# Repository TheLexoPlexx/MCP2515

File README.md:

# MCP2515
KiCad-Files for the commonly found MCP2515 CAN Controller and Transceiver used in plenty of arduino-Projects.

Schematic is not my own.

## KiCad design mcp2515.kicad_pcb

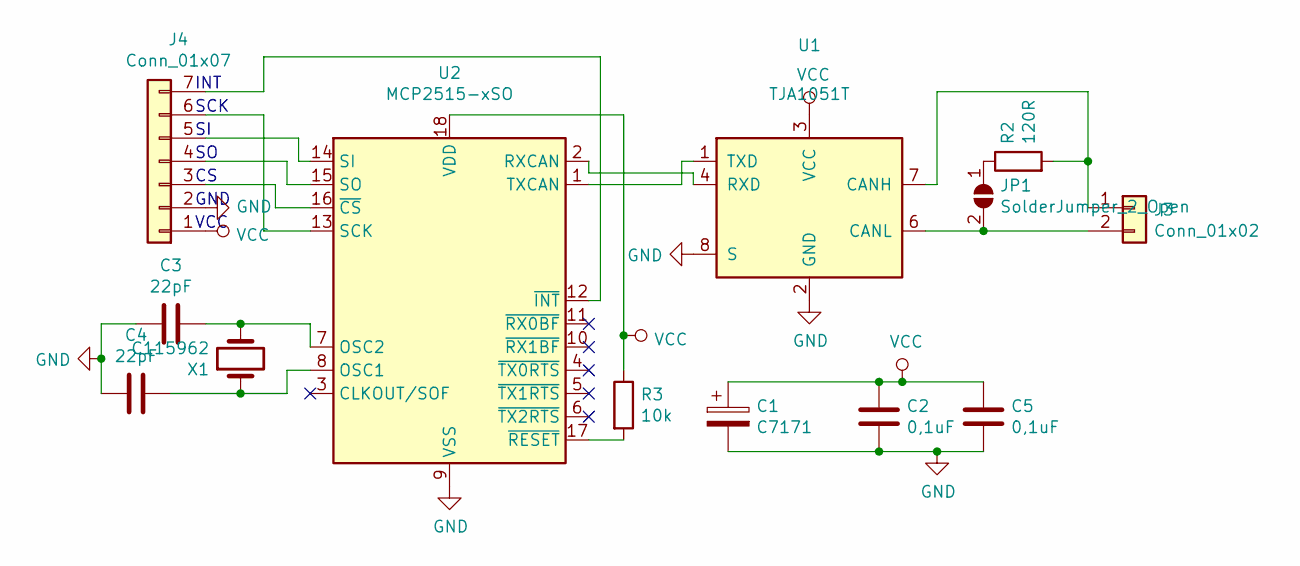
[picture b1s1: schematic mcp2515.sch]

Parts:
C1: C7171; R_1206_3216Metric
C2, C5: 0,1uF; C_0201_0603Metric
C3, C4: 22pF; C_0201_0603Metric
J3: Conn_01x02; PinHeader_1x02_P2.54mm_Vertical
J4: Conn_01x07; PinHeader_1x07_P2.54mm_Vertical
JP1: SolderJumper_2_Open; SolderJumper-2_P1.3mm_Open_Pad1.0x1.5mm
R2: 120R; R_0603_1608Metric
R3: 10k; R_0603_1608Metric
U1: TJA1051T; SOIC-8_3.9x4.9mm_P1.27mm
U2: MCP2515-xSO; SOIC-18W_7.5x11.6mm_P1.27mm
X1: C115962; Crystal_SMD_5032-2Pin_5.0x3.2mm

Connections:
GND: C1.2, C2.2, C3.2, C4.2, C5.2, J4.2, U1.2 (GND), U1.8 (S), U2.9 (VSS)
unnamed: C3.1, U2.7 (OSC2), X1.2
unnamed: C4.1, U2.8 (OSC1), X1.1
unnamed: J3.1, R2.2, U1.7 (CANH)
unnamed: J3.2, JP1.2 (B), U1.6 (CANL)
unnamed: J4.3, U2.16 (~CS)
unnamed: J4.4, U2.15 (SO)
unnamed: J4.5, U2.14 (SI)
unnamed: J4.6, U2.13 (SCK)
unnamed: J4.7, U2.12 (~INT)
unnamed: JP1.1 (A), R2.1
unnamed: R3.2, U2.17 (~RESET)
unnamed: U1.1 (TXD), U2.1 (TXCAN)
unnamed: U1.4 (RXD), U2.2 (RXCAN)
VCC: C1.1, C2.1, C5.1, J4.1, R3.1, U1.3 (VCC), U2.18 (VDD)

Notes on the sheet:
VCC
GND
SCK
INT

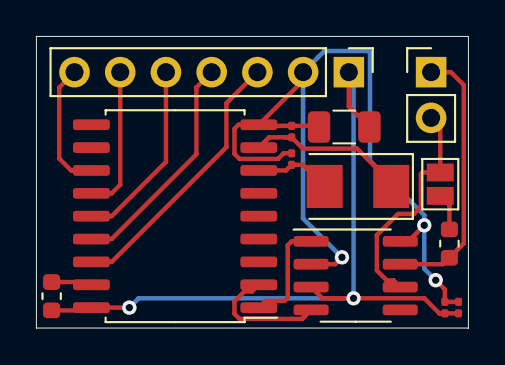
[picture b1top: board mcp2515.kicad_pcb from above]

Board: 2 copper layers, 24.0 x 16.2 mm, 13 parts (0 on the bottom side), 15 nets.

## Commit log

2020-04-13 Added schematic.png
2020-04-13 Added .gitattributes
2020-04-26 Added Values for Capacitors, added Footprints
2020-04-29 Updated, added Capacitors
2020-04-29 Ignores gerber-Folder now
